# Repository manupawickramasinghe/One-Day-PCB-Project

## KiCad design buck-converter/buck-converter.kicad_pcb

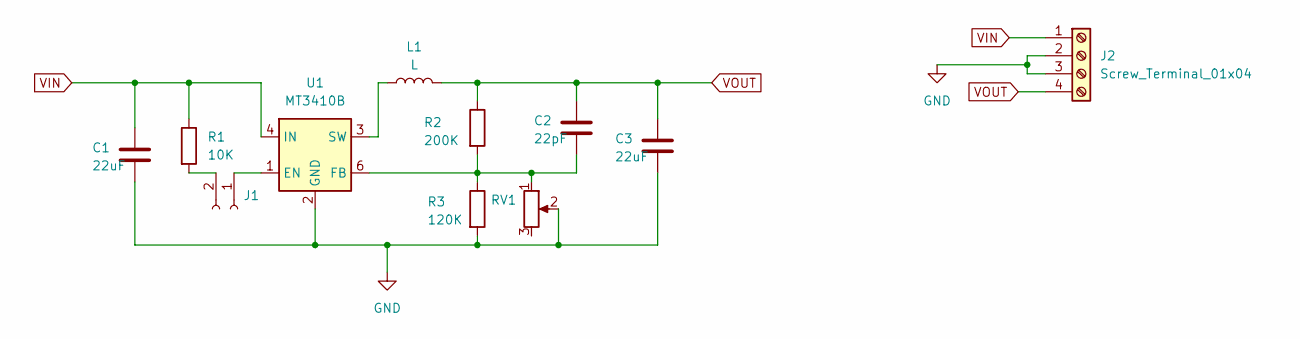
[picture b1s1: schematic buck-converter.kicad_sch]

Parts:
C1, C3: 22uF; C_0805_2012Metric
C2: 22pF; C_0805_2012Metric
J1: Conn_01x02_Socket; PinSocket_1x02_P2.54mm_Vertical
J2: Screw_Terminal_01x04; TerminalBlock_4Ucon_1x04_P3.50mm_Horizontal
L1: L; CDRH74NP120MCB
R1: 10K; R_0805_2012Metric_Pad1.20x1.40mm_HandSolder
R2: 200K; R_0805_2012Metric_Pad1.20x1.40mm_HandSolder
R3: 120K; R_0805_2012Metric_Pad1.20x1.40mm_HandSolder
RV1: R_Potentiometer; Potentiometer_Bourns_3386C_Horizontal
U1: MT3410B; SOT-23-6

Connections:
GND: C1.2, C3.2, J2.2, J2.3, R3.2, RV1.2, U1.2 (GND)
unnamed: J1.1, U1.1 (EN)
unnamed: J1.2, R1.2
unnamed: C2.2, R2.2, R3.1, RV1.1, U1.6 (FB)
unnamed: L1.1, U1.3 (SW)
VIN: C1.1, J2.1, R1.1, U1.4 (IN)
VOUT: C2.1, C3.1, J2.4, L1.2, R2.1

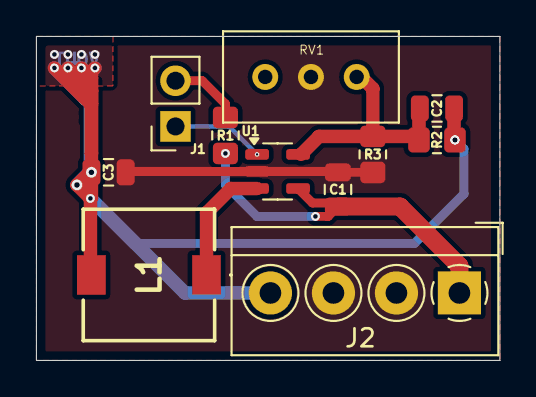
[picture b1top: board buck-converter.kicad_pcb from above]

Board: 2 copper layers, 25.8 x 18.0 mm, 12 parts (1 on the bottom side), 7 nets.

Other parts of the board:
kibuzzard-670ED8D1: G***; kibuzzard-670ED8D1
